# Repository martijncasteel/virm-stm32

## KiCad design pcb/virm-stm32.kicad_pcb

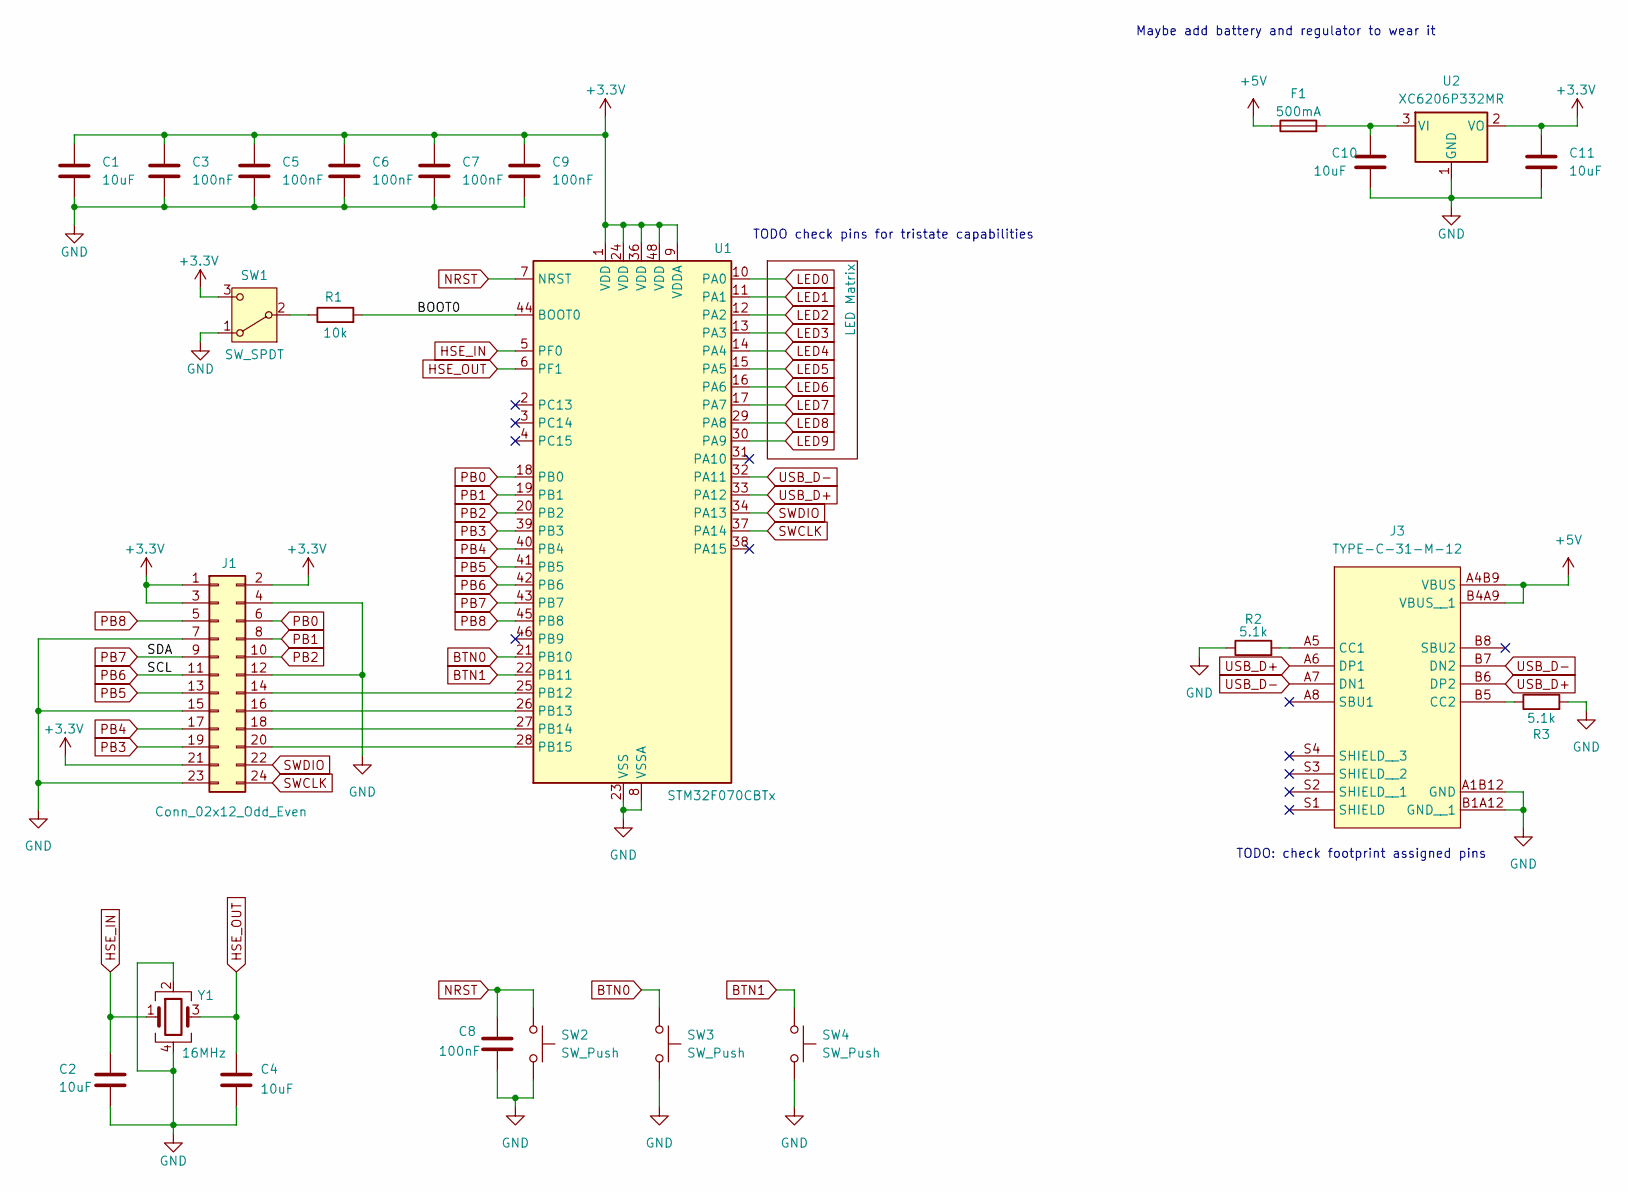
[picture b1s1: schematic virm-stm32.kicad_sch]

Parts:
C1, C2, C4, C10, C11: 10uF; C_0402_1005Metric; lcsc C15525
C3, C5, C6, C7, C8, C9: 100nF; C_0402_1005Metric; lcsc C1525
F1: 500mA; Fuse_0603_1608Metric; lcsc C261937
J1: Conn_02x12_Odd_Even; PinHeader_2x12_P2.54mm_Vertical
J3: TYPE-C-31-M-12; lcsc C165948
R1: 10k; R_0603_1608Metric; lcsc C25804
R2, R3: 5.1k; R_0603_1608Metric; lcsc C23186
SW1: SW_SPDT; SW_SPDT_PCM12; lcsc C778186
SW2, SW3, SW4: SW_Push; SW_Push_1P1T_XKB_TS-1187A; lcsc C318884
U1: STM32F070CBTx; LQFP-48_7x7mm_P0.5mm; lcsc C74909
U2: XC6206P332MR; SOT-23-3; lcsc C5446
Y1: 16MHz; Crystal_SMD_3225-4Pin_3.2x2.5mm; lcsc C112972

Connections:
+3.3V: C1.1, C3.1, C5.1, C6.1, C7.1, C9.1, C11.1, J1.1, J1.2, J1.3, J1.21, SW1.3 (C), U1.1 (VDD), U1.9 (VDDA), U1.24 (VDD), U1.36 (VDD), U1.48 (VDD), U2.2 (VO); also elsewhere on the board
+5V: F1.1, J3.A4B9 (VBUS), J3.B4A9 (VBUS__1)
/BOOT0: R1.2, U1.44 (BOOT0)
BTN0: SW3.1, U1.21 (PB10)
BTN1: SW4.1, U1.22 (PB11)
GND: C1.2, C2.2, C3.2, C4.2, C5.2, C6.2, C7.2, C8.2, C9.2, C10.2, C11.2, J1.4, J1.7, J1.12, J1.15, J1.23, J3.A1B12 (GND), J3.B1A12 (GND__1), R2.1, R3.2, SW1.1 (A), SW2.2, SW3.2, SW4.2, U1.8 (VSSA), U1.23 (VSS), U1.35 (VSS), U1.47 (VSS), U2.1 (GND), Y1.2, Y1.4; also elsewhere on the board
HSE_IN: C2.1, U1.5 (PF0), Y1.1
HSE_OUT: C4.1, U1.6 (PF1), Y1.3
LED0: U1.10 (PA0); also elsewhere on the board
LED1: U1.11 (PA1); also elsewhere on the board
LED2: U1.12 (PA2); also elsewhere on the board
LED3: U1.13 (PA3); also elsewhere on the board
LED4: U1.14 (PA4); also elsewhere on the board
LED5: U1.15 (PA5); also elsewhere on the board
LED6: U1.16 (PA6); also elsewhere on the board
LED7: U1.17 (PA7); also elsewhere on the board
LED8: U1.29 (PA8); also elsewhere on the board
LED9: U1.30 (PA9); also elsewhere on the board
NRST: C8.1, SW2.1, U1.7 (NRST); also elsewhere on the board
unnamed: J1.14, U1.25 (PB12)
unnamed: J1.16, U1.26 (PB13)
unnamed: J1.18, U1.27 (PB14)
unnamed: J1.20, U1.28 (PB15)
unnamed: J3.A5 (CC1), R2.2
unnamed: J3.B5 (CC2), R3.1
unnamed 35: R1.1, SW1.2 (B); also elsewhere on the board
unnamed: C10.1, F1.2, U2.3 (VI)
PB0: J1.6, U1.18 (PB0)
PB1: J1.8, U1.19 (PB1)
PB2: J1.10, U1.20 (PB2)
PB3: J1.19, U1.39 (PB3)
PB4: J1.17, U1.40 (PB4)
PB5: J1.13, U1.41 (PB5)
PB6: J1.11, U1.42 (PB6)
PB7: J1.9, U1.43 (PB7)
PB8: J1.5, U1.45 (PB8)
SWCLK: J1.24, U1.37 (PA14)
SWDIO: J1.22, U1.34 (PA13)
USB_D+: J3.A6 (DP1), J3.B6 (DP2), U1.33 (PA12)
USB_D-: J3.A7 (DN1), J3.B7 (DN2), U1.32 (PA11)

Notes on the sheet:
TODO check pins for tristate capabilities
TODO: check footprint assigned pins
Maybe add battery and regulator to wear it

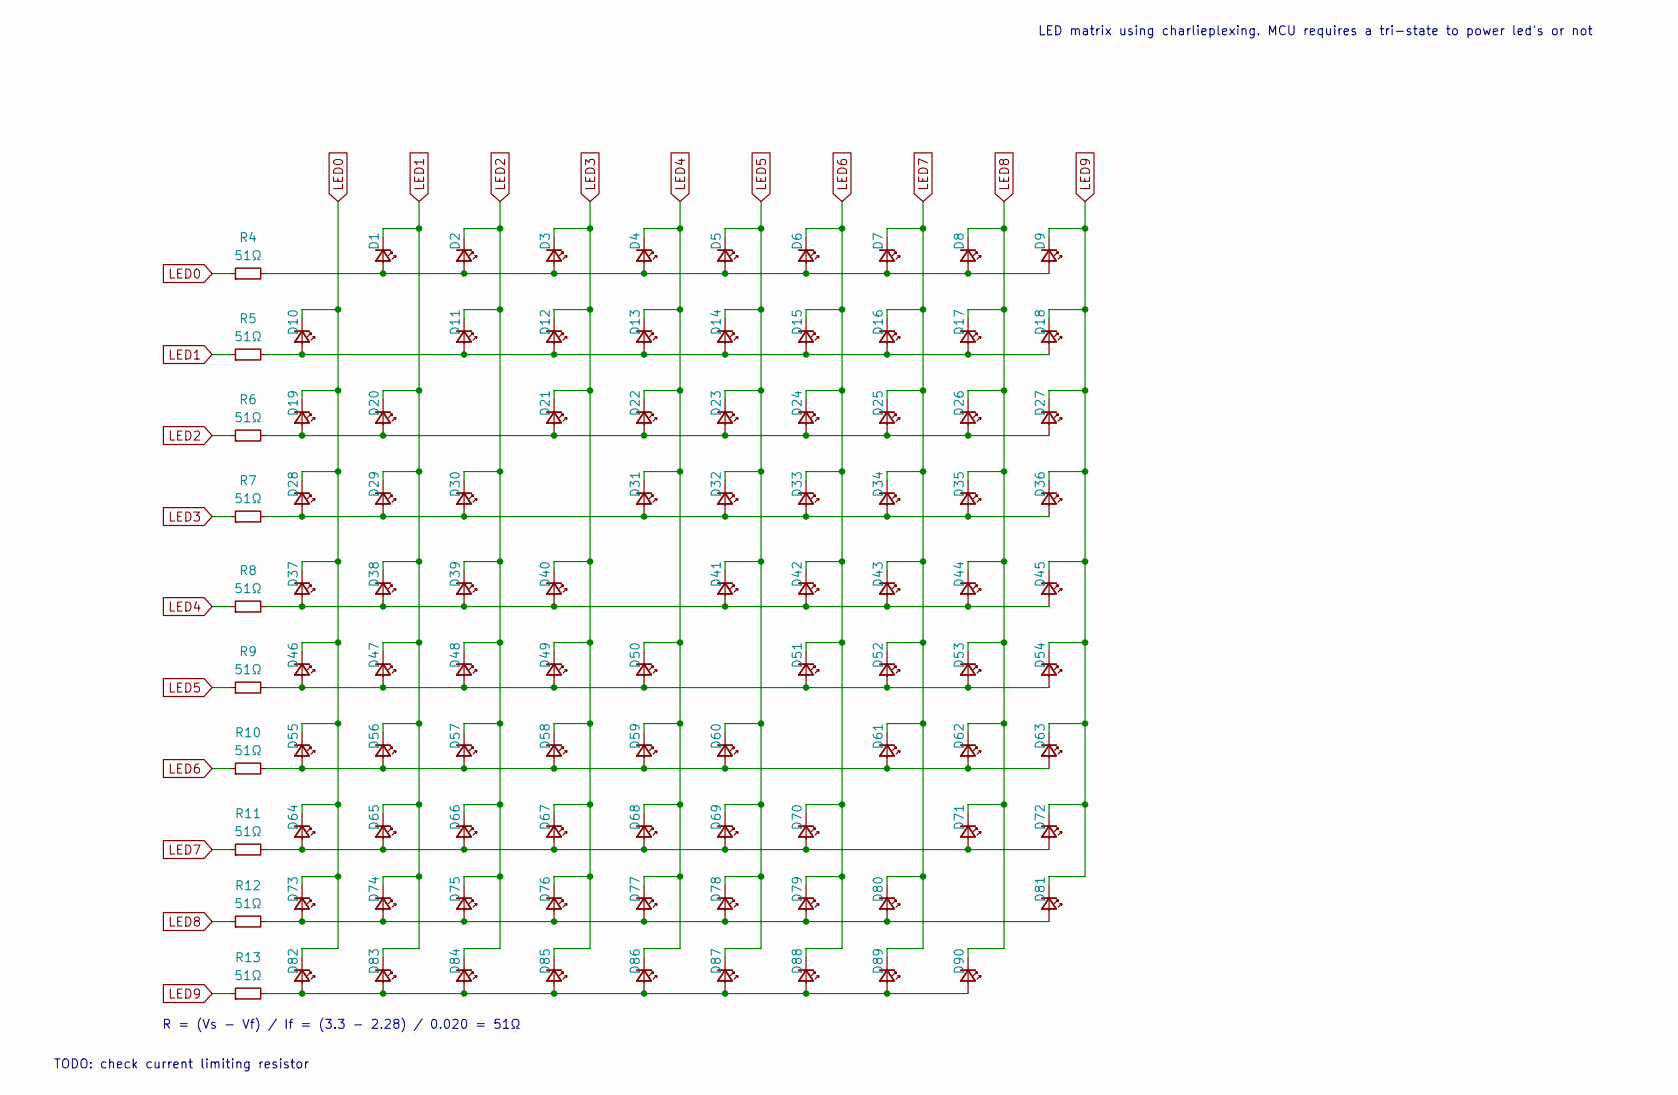
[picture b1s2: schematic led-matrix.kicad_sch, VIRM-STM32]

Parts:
D1, D2, D3, D4, D5, D6, D7, D8, D9, D10, D11, D12, D13, D14, D15, D16, D17, D18, D19, D20, D21, D22, D23, D24, D25, D26, D27, D28, D29, D30, D31, D32, D33, D34, D35, D36, D37, D38, D39, D40, D41, D42, D43, D44, D45, D46, D47, D48, D49, D50, D51, D52, D53, D54, D55, D56, D57, D58, D59, D60, D61, D62, D63, D64, D65, D66, D67, D68, D69, D70, D71, D72, D73, D74, D75, D76, D77, D78, D79, D80, D81, D82, D83, D84, D85, D86, D87, D88, D89, D90: LED_Small; LED_0805_2012Metric; lcsc C84256
R4, R5, R6, R7, R8, R9, R10, R11, R12, R13: 51Ω; R_0603_1608Metric; lcsc C23197

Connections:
LED0: D10.1 (K), D19.1 (K), D28.1 (K), D37.1 (K), D46.1 (K), D55.1 (K), D64.1 (K), D73.1 (K), D82.1 (K), R4.1; also elsewhere on the board
LED1: D1.1 (K), D20.1 (K), D29.1 (K), D38.1 (K), D47.1 (K), D56.1 (K), D65.1 (K), D74.1 (K), D83.1 (K), R5.1; also elsewhere on the board
LED2: D2.1 (K), D11.1 (K), D30.1 (K), D39.1 (K), D48.1 (K), D57.1 (K), D66.1 (K), D75.1 (K), D84.1 (K), R6.1; also elsewhere on the board
LED3: D3.1 (K), D12.1 (K), D21.1 (K), D40.1 (K), D49.1 (K), D58.1 (K), D67.1 (K), D76.1 (K), D85.1 (K), R7.1; also elsewhere on the board
LED4: D4.1 (K), D13.1 (K), D22.1 (K), D31.1 (K), D50.1 (K), D59.1 (K), D68.1 (K), D77.1 (K), D86.1 (K), R8.1; also elsewhere on the board
LED5: D5.1 (K), D14.1 (K), D23.1 (K), D32.1 (K), D41.1 (K), D60.1 (K), D69.1 (K), D78.1 (K), D87.1 (K), R9.1; also elsewhere on the board
LED6: D6.1 (K), D15.1 (K), D24.1 (K), D33.1 (K), D42.1 (K), D51.1 (K), D70.1 (K), D79.1 (K), D88.1 (K), R10.1; also elsewhere on the board
LED7: D7.1 (K), D16.1 (K), D25.1 (K), D34.1 (K), D43.1 (K), D52.1 (K), D61.1 (K), D80.1 (K), D89.1 (K), R11.1; also elsewhere on the board
LED8: D8.1 (K), D17.1 (K), D26.1 (K), D35.1 (K), D44.1 (K), D53.1 (K), D62.1 (K), D71.1 (K), D90.1 (K), R12.1; also elsewhere on the board
LED9: D9.1 (K), D18.1 (K), D27.1 (K), D36.1 (K), D45.1 (K), D54.1 (K), D63.1 (K), D72.1 (K), D81.1 (K), R13.1; also elsewhere on the board
unnamed: D1.2 (A), D2.2 (A), D3.2 (A), D4.2 (A), D5.2 (A), D6.2 (A), D7.2 (A), D8.2 (A), D9.2 (A), R4.2
unnamed: D10.2 (A), D11.2 (A), D12.2 (A), D13.2 (A), D14.2 (A), D15.2 (A), D16.2 (A), D17.2 (A), D18.2 (A), R5.2
unnamed: D19.2 (A), D20.2 (A), D21.2 (A), D22.2 (A), D23.2 (A), D24.2 (A), D25.2 (A), D26.2 (A), D27.2 (A), R6.2
unnamed: D28.2 (A), D29.2 (A), D30.2 (A), D31.2 (A), D32.2 (A), D33.2 (A), D34.2 (A), D35.2 (A), D36.2 (A), R7.2
unnamed: D37.2 (A), D38.2 (A), D39.2 (A), D40.2 (A), D41.2 (A), D42.2 (A), D43.2 (A), D44.2 (A), D45.2 (A), R8.2
unnamed: D46.2 (A), D47.2 (A), D48.2 (A), D49.2 (A), D50.2 (A), D51.2 (A), D52.2 (A), D53.2 (A), D54.2 (A), R9.2
unnamed: D55.2 (A), D56.2 (A), D57.2 (A), D58.2 (A), D59.2 (A), D60.2 (A), D61.2 (A), D62.2 (A), D63.2 (A), R10.2
unnamed: D64.2 (A), D65.2 (A), D66.2 (A), D67.2 (A), D68.2 (A), D69.2 (A), D70.2 (A), D71.2 (A), D72.2 (A), R11.2
unnamed: D73.2 (A), D74.2 (A), D75.2 (A), D76.2 (A), D77.2 (A), D78.2 (A), D79.2 (A), D80.2 (A), D81.2 (A), R12.2
unnamed: D82.2 (A), D83.2 (A), D84.2 (A), D85.2 (A), D86.2 (A), D87.2 (A), D88.2 (A), D89.2 (A), D90.2 (A), R13.2

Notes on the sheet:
R = (Vs - Vf) / If = (3.3 - 2.28) / 0.020 = 51Ω
LED matrix using charlieplexing. MCU requires a tri-state to power led's or not
TODO: check current limiting resistor

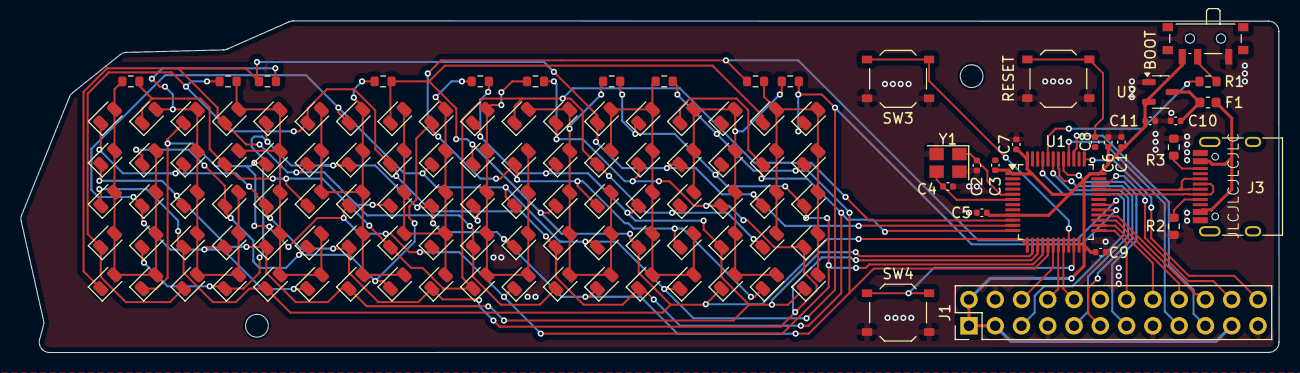
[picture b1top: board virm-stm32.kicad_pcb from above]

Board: 2 copper layers, 121.6 x 32.1 mm, 124 parts (0 on the bottom side), 49 nets.

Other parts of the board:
BOOT: SW_SPDT; SW_SPDT_PCM12
RESET: SW_Push; SW_Push_1P1T_XKB_TS-1187A

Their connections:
+3.3V: BOOT.3 (C); also elsewhere on the board
GND: BOOT.1 (A), RESET.2; also elsewhere on the board
NRST: RESET.1; also elsewhere on the board
unnamed 35: BOOT.2 (B); also elsewhere on the board

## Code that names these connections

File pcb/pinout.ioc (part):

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Mcu.Name=STM32F070CBTx
Mcu.Package=LQFP48
Mcu.UserName=STM32F070CBTx
PA11.Mode=Device
PA11.Signal=USB_DM
PA12.Mode=Device
PA12.Signal=USB_DP
PA13.Mode=Serial_Wire
PA13.Signal=SYS_SWDIO
PA14.Mode=Serial_Wire
PA14.Signal=SYS_SWCLK
PB6.Mode=I2C
PB6.Signal=I2C1_SCL
PB7.Mode=I2C
PB7.Signal=I2C1_SDA
PF0-OSC_IN.Mode=HSE-External-Oscillator
PF0-OSC_IN.Signal=RCC_OSC_IN
PF1-OSC_OUT.Mode=HSE-External-Oscillator
PF1-OSC_OUT.Signal=RCC_OSC_OUT
RCC.HSE_VALUE=16000000
RCC.SYSCLKFreq_VALUE=48000000
RCC.SYSCLKSource=RCC_SYSCLKSOURCE_PLLCLK
board=custom

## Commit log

2024-03-10 Initial setup for VIRM-STM32
2024-03-16 Initial version
2024-03-16 Added a power circuit
2024-03-24 Added a led matrix using charlieplexing
2024-03-24 Added footprints, except for the USB port
2024-04-08 Added footprint for usb port
2024-04-12 Started working on PCB layout
2024-05-07 started routing, with additional leds
2024-05-08 First attempt at routing, also move the serial wire debug to the same header as the other IO's
2024-05-08 Added new board outline
